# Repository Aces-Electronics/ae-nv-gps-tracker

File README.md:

# AE-SIM7080G-S3 NB-IoT Tracker

LilyGo T-SIM7080G-S3 based GPS tracker with NB-IoT connectivity for the AE-NV ecosystem.

## Hardware

- **Board**: LilyGo T-SIM7080G-S3 (ESP32-S3 + SIM7080G modem)
- **GPS**: Integrated GNSS (GPS/GLONASS/Beidou/Galileo)
- **Connectivity**: NB-IoT / LTE Cat-M1
- **Battery**: LiPo with AXP2101 PMU
- **Daughter board**: `ae-tracker-db` — LIS3DH accelerometer, SN65HVD231 CAN
  transceiver, and a BQ25176J charger that tops the LiPo up from the jetski's
  supply through an MCU-switchable cutoff. Plugs onto the LilyGo's 16-pin
  expansion header; the J4 pin map is in [`src/utilities.h`](src/utilities.h).

## Features

- ✅ GPS tracking with satellite count and HDOP
- ✅ NB-IoT connectivity via Telstra network
- ✅ MQTT telemetry publishing to AE-NV backend
- ✅ BLE configuration and diagnostics (15s window on cold boot, held open
  while a phone stays connected)
- ✅ Orientation detection (Flat/Vertical/Upside Down) — needs the daughter
  board; reports `Unknown` without it
- ✅ Configurable reporting intervals (1-60 minutes)
- ✅ Battery voltage monitoring
- ✅ Deep sleep between reports, with GPS-failure backoff
- ✅ **Daily heartbeat + wake on motion** — the timer is proof of life; movement
  is what actually triggers a report
- ✅ **Adaptive motion threshold** — climbs when the tracker keeps waking for
  movement GPS says didn't happen, drops straight back on real travel
- ✅ **Jetski engine data over CAN** — rpm, coolant, engine hours and iBR
  trim position decoded from the ECU (daughter board). See
  [`docs/can/seadoo-can.md`](docs/can/seadoo-can.md).

## Telemetry Fields

The tracker publishes the following data via MQTT:

```json
{
  "mac": "860016043157614",
  "model": "ae-sim7080g-tracker",
  "fix": true,               // Did this wake get a GPS fix at all
  "lat": -28.02575,          // lat/lon/alt/speed/sats/hdop are omitted if !fix
  "lon": 153.3879,
  "alt": -11.981,
  "speed": 0,
  "sats": 11,
  "supply_adc_raw": 9216,    // Ski supply, raw LIS3DH aux-ADC count
  "supply_voltage": 12.18,   // ...converted, once calibrated (absent if not)
  "voltage": 0.00,           // USB VBUS placeholder, debug frames only
  "device_voltage": 4.177,   // Internal battery voltage
  "battery_voltage": 4.177,  // Legacy alias
  "rssi": 19,
  "orientation": "Flat",
  "charge_state": "Charging",  // Charging | Idle | Fault | No Input
  "supply_enabled": true,      // Is the jetski allowed to feed the charger
  "wake_reason": "Motion",     // Cold Boot | Timer | Motion
  "accel_up": 1.00,            // Vehicle frame, g. Omitted if no IMU
  "accel_fwd": -0.02,
  "accel_stbd": 0.03,
  "engine_bus": true,          // Was the ski's CAN bus awake at all
  "ski_running": true,         // Drives the reporting cadence
  "rpm": 1455,                 // Omitted unless engine_bus
  "coolant_raw": 110,          // 0x102 b3, raw count — identity confirmed,
                               //   scaling not. raw-40 gives a believable 70C
  "engine_temp_raw": 140,      // 0x342 b4, raw count. NOT the coolant temp —
                               //   kept because it is a real signal, unidentified
  "engine_minutes": 5856,      // 0x342 b6:b7. Confirmed against the dash to the
                               //   minute: 5856 = 97h36m
  "ibr_trim": 5,               // 0x012 b2, iBR up/down position, 1..9
  "motion_sensitivity": "Medium", // Low | Medium | High -- the selected floor
  "motion_threshold_mg": 352,  // Where the adaptive ladder currently sits
  "motion_suppressed": 0,      // Motion wakes rate-limited away since last report
  "interval": 5,               // The RUNNING interval. A parked ski ignores it
  "next_wake_mins": 60         // When the next frame is actually due
}
```

## Development

### Prerequisites

- PlatformIO CLI or IDE
- USB-C cable for flashing

### Building & Flashing

```bash
# Build firmware
pio run -d /path/to/ae-sim7080g-tracker

# Flash to device
pio run -d /path/to/ae-sim7080g-tracker -t upload --upload-port /dev/ttyACM6

# Monitor serial output
pio device monitor --port /dev/ttyACM6 -b 115200
```

### CAN bring-up build

A separate environment boots straight into a listen-only CAN sniffer and never
reaches the tracker's normal cycle — no modem, no MQTT, no sleep:

```bash
pio run -e can-sniffer -t upload && pio device monitor -b 115200
```

It scans 250k → 500k → 125k, keeps whichever rate hears frames, prints a table
of distinct IDs with hit counts and per-byte ranges, then runs one probe: an
8-second learn phase, a single `*** GO ***`, and a 40-second window that records
every frame **and** narrates which bytes changed while you work a control.

The learn phase is the trick. It marks every byte that moves while the vehicle
is left alone — engine signals, counters, checksums — so afterwards it can
report only the bytes that held still and then moved. Operate one control and
the output is a short list naming that control's bytes.

Two things worth knowing before relying on it:

- **It prints its own blind spot.** A byte that moved during learning is hidden
  from the narration, which permanently hides both halves of any multiplexed
  signal. The excluded bytes are listed up front, and the CSV has every frame
  regardless — the narration is a convenience, the CSV is the evidence.
- **One prompt, then it halts.** Earlier versions recorded and narrated in
  separate phases with a `GO` for each, and the natural thing was to act on the
  second one, which was no longer recording. Three sessions were lost that way.

This is how the iBR up/down decode was found: the position byte and its command
byte both showed up in the narration within seconds of pressing a button.

**Listen-only never drives the bus**, not even the ACK bit, so this is safe to
plug into a running ski before anything is known about the bus or its rate. The
shipping firmware is unaffected — `default_envs` keeps this out of a bare
`pio run`, and the linker drops the sniffer and the TWAI driver from it.

Note that the daughter board's CAN termination jumper (JP1) is bridged by
default. A vehicle bus is already terminated at both ends, so JP1 most likely
wants cutting before connecting to a real ski.

### Configuration

The tracker can be configured via BLE during the 15-second window on cold boot,
or by holding the boot button through a reset. A connected client holds the
window open for as long as it stays, up to a five-minute ceiling — 15 seconds
is less than a connect, a service discovery and a look at the screen, so without
that the app was routinely cut off mid-session by the device closing BLE
underneath it. The ceiling is what stops a phone left connected in somebody's
pocket from holding the tracker out of deep sleep indefinitely.

- **Report Interval**: 1-60 minutes
- **Home Location**: Set via web UI
- **Admin Mode**: Forces 1-minute intervals for testing

#### BLE characteristics

Service `4fafc203-1fb5-459e-8fcc-c5c9c331914b`.

| Characteristic | UUID suffix | Direction | Payload |
| --- | --- | --- | --- |
| GPS | `…2030` | read/notify | `lat,lon,speed,sats,hdop,sats_in_view,fix` |
| Status | `…2031` | read/notify | `volts,soc,csq,Net: <creg>` |
| Name | `…2040` | read/write | device name suffix |
| Interval | `…2050` | read/write | uint32 LE, minutes |
| Motion sensitivity | `…2051` | read/write | one byte, 0 Low / 1 Medium / 2 High |
| Verbose telemetry | `…2052` | read/write | one byte, 0 off / non-zero on |
| Diagnostics: Device | `…2060` | read/notify | JSON |
| Diagnostics: Position | `…2061` | read/notify | JSON |
| Diagnostics: Power | `…2062` | read/notify | JSON |
| Diagnostics: Motion | `…2063` | read/notify | JSON |
| Diagnostics: Engine | `…2064` | read/notify | JSON |
| Pairing | `ACDC1234-…-1234567890CB` | read (encrypted) | trigger only |

Plus APN (`ae000101-…`) and the MQTT broker/user/pass characteristics
(`…2645`/`…2646`/`…2647`).

#### Pairing and what is gated

Bonding with MITM protection and Secure Connections, with a six-digit passkey
derived from the last three bytes of the Wi-Fi base MAC — the same derivation
every other AE product uses, and the same one the app displays.

This was previously off: the source said `// Security DISABLED for verification`,
which meant the PIN the app showed on the tracker screen was decoration. Nothing
ever asked for it, and anyone within radio range during a config window could
rewrite the APN, the broker and the MQTT credentials.

What is gated, and what is not:

- **Open** — the GPS and status characteristics. Someone close enough to read
  these over BLE is close enough to see the ski, so gating them buys little, and
  leaving them open means the app's basic screen works without a bond.
- **Encrypted (`READ_ENC`)** — all five diagnostics sections.
- **Encrypted (`WRITE_ENC`, and `READ_ENC` where readable)** — every
  configuration characteristic: name, APN, broker, MQTT user and password,
  interval, motion sensitivity, verbose telemetry.

The app reads the pairing characteristic on connect purely to force the link to
encrypt before it subscribes to anything — a subscribe on an encrypted
characteristic across an unencrypted link fails, and it fails quietly. That read
is service-agnostic in the app, so exposing the characteristic is all that was
needed on this side.

The device has no display, so the PIN comes from the app: it is shown against
the device while it is being connected to (which is when the OS prompts for it)
and on the tracker's own screen afterwards. It is also printed to the serial
console on every connect.

The GPS line's last two fields were appended to what was a five-field format,
so an older app reads the first five and ignores the rest. `sats_in_view` is the
number that moves during acquisition — `sats` counts the ones used in a fix and
sits at zero until there is one, so a screen showing only that looks broken for
two minutes and then works.

The five diagnostics characteristics carry the whole telemetry report, section
by section, refreshed once a second while a client is connected. They are built
by `buildTelemetry()` — the same function that builds the MQTT frame — so what
the app's debug screen shows is what the device publishes, by construction. They
are sectioned because a BLE characteristic value stops at 512 bytes and a full
verbose report is about twice that; `buildTelemetry()` decides which section each
field belongs to, so a field added later has to be given a home rather than
quietly failing to reach BLE.

Unlike the MQTT frame, the diagnostics are **always verbose**. The
`debug_payload` setting decides what is worth paying for over the cellular link;
it has nothing to say about what a phone already standing next to the ski may
look at.

## Debugging & Troubleshooting

### Serial Monitor

Monitor real-time debug output:

```bash
pio device monitor --port /dev/ttyACM0 -b 115200
```

### Debug Logging

The firmware includes comprehensive diagnostic logging:

**GPS Acquisition:**
```
[DEBUG] Raw CGNSINF: 1,1,20260206025753.000,-28.025740,153.387809,...
GPS FIX! Sats: 10 (lat: -28.02574, lon: 153.38780)
```

**Network Registration:**
```
[DEBUG] Checking network status...
[DEBUG] CEREG: +CEREG: 0,2  // 0,2 = registered on home network
[DEBUG] COPS: +COPS: 0,0,"Telstra Mobile",7  // Connected operator
[DEBUG] Signal Quality after registration: 20  // RSSI in dBm
```

**MQTT Publish:**
```
[DEBUG] Using Topic: ae-nv/tracker/860016043157614/up
[MQTT] Publishing Payload: {"mac":"860016043157614",...}
[MQTT] Publish OK
```

### Common Issues

**No GPS Fix:**
- Cold start can take 2-5 minutes
- Ensure clear view of sky
- Check antenna connection

**Network Registration Fails:**
- Verify SIM card is inserted and activated
- Check CEREG response: `0,0` = not registered, `0,2` = registered
- CSQ 99 = unknown signal (modem issue)
- CSQ 0-31 = valid signal strength

**MQTT Publish Fails:**
- Verify network registration succeeded first
- Check APN settings (default: `telstra.internet`)
- Ensure MQTT broker is reachable

**Device Not Appearing in UI:**
- Check MQTT payload in serial output
- Verify `mac` field matches device ID
- Check backend worker logs for ingestion errors
- Confirm device is claimed to your account

### Enable TinyGSM Debug

For detailed AT command logging, uncomment in `platformio.ini`:

```ini
build_flags = 
    -DTINY_GSM_DEBUG=Serial
```

This will show all modem AT commands and responses.

## Architecture

### GPS Parsing

The firmware uses robust satellite count parsing with fallback logic:
- Primary: "Satellites Used" from `+CGNSINF` response (index 15)
- Fallback: "Satellites in View" (index 14) when used count is unavailable

### Voltage Nomenclature

- `voltage`: External supply voltage (0.00V placeholder for future charging hardware)
- `device_voltage`: Internal PMU battery voltage (~4.2V when fully charged)
- `battery_voltage`: Legacy field for backward compatibility

### Power Management

- **Active Mode**: GPS acquisition + MQTT publish
- **BLE Window**: 15 seconds on cold boot, extended while a client is
  connected, to a five-minute ceiling
- **Charge cutoff**: the jetski feed is cut above **4.10V** and restored below
  **3.70V**, decided at report time against the PMU's battery reading and
  latched across sleep in RTC memory.

  4.10V sits *below* the BQ25176J's 4.2V regulation point, so the firmware —
  not the charger — is what ends a charge, opening the switch on the way up
  before the cell is ever held at full. The wide gap down to 3.70V is what makes
  that worth doing: a LiPo ages fastest sitting at full charge, so the pair
  cycles the cell through roughly 3.7–4.1 rather than floating it at 4.2. With
  only a sleeping tracker as a load, one traverse of that band takes a long time,
  so it costs very few cycles to buy. Both thresholds read the AXP2101's *cell*
  voltage — the jetski's own voltage is not available to decide on until the
  supply-sense divider is reworked.
- **Deep Sleep**: Cadence follows the ski, not the clock.
  - **Running** (CAN bus awake) → the configured `report_interval_mins`,
    5 minutes by default, settable over BLE. GPS-failure backoff applies
    (5/15/30/60/180 min).
  - **Parked** → a **1440-minute (daily) heartbeat**. GPS-failure backoff is not
    applied; stretching a day further on one missed fix trades away the only
    thing a heartbeat is for.

    **A parked heartbeat that fails to publish is retried sooner**, at 60 → 180
    → 360 minutes before falling back to the daily cadence. Without this, one
    bad modem session meant 48 hours of silence — and silence is
    indistinguishable from a stolen ski, a flat battery, or a dead tracker.
    Escalating rather than fixed because the usual cause is no coverage, and
    retrying hourly forever in a dead zone spends exactly the battery the daily
    cadence exists to protect.

    Note the daily timer is clocked by the ESP32's **internal RC oscillator**,
    not a crystal, so a 1440-minute sleep can legitimately land up to roughly an
    hour either side. A heartbeat that is late by tens of minutes is normal; one
    that is hours late is not.

  CAN traffic is the running signal because the ski's bus only wakes with the
  ignition. Supply voltage above ~13V would be the better test — it survives a
  CAN fault — but the supply-sense divider is mis-scaled and reads nothing
  usable yet (see `R15`/`R16` in [`src/utilities.h`](src/utilities.h)).
- **Wake on motion**: The LIS3DH interrupt is an `ext1` deep-sleep wake source.
  Motion reports are rate-limited to one per 120s, checked before the modem is
  powered, so a suppressed wake costs ~200ms rather than a GPS acquisition.

  **Tapping the board will not wake it, and that is the design.** `INT1_DURATION`
  is counted in ODR periods, so the default three samples at 50Hz require 60ms
  of *continuous* over-threshold motion, and normal mode band-limits to roughly
  ODR/2 = 25Hz before the comparator sees anything. A finger tap is a few
  milliseconds of mostly high-frequency energy — filtered down, and over long
  before the duration counter arrives. Shake the board instead.

  To check the path live rather than by waiting out a sleep cycle, the
  `db-bench` build watches INT1 for 15 seconds on startup and prints every
  latched event with the axes that caused it.

  On every wake from sleep the firmware reads the LIS3DH's interrupt block back
  *before* re-arming it and says whether it survived. Those registers are
  volatile, so retained values prove the part held its 3.3V rail through the
  sleep and reset defaults prove it did not — which settles the question a
  missed wake otherwise only raises. (It should always survive: the daughter
  board's 3V3 is J4.1 = AXP2101 DCDC1, the same rail that keeps the ESP32's own
  RTC domain alive. Nothing in this firmware touches DCDC1.)
- **Motion sensitivity**: three selectable levels, each setting the **floor** of
  the adaptive ladder rather than a fixed threshold — the ski still finds its own
  level from wherever it starts. Values are chosen against a *measured* noise
  floor of 24mg (high-pass filter settled, board at rest), so the margins are
  known rather than guessed:

  | Level | Floor | Margin | Ceiling | For |
  |---|---|---|---|---|
  | Low | 704mg | ~29× noise | 2032mg | A deliberate shove; a ski somewhere lively, where less would report the weather |
  | **Medium** | **352mg** | ~15× noise | **1408mg** | **Shipped default.** Registers ordinary handling |
  | High | 256mg | ~11× noise | 1024mg | A quiet mooring, where a nudge should count |

  These were **doubled** from an original 352/176/128 after the first real
  deployment: a unit on Medium riding in a car woke nine times in 65 minutes and
  spent the hour climbing away from a floor too low to start from. The old
  Medium is the new Low, which is the honest description of what 176mg proved
  to be worth.

  All three sit exactly on the `INT1_THS` grid (16mg steps at ±2g) — 44, 22 and
  16 counts — so none truncate. Worth checking when retuning: 56mg, for example,
  is not representable and would silently become 48mg, only 2× the noise floor.

  Settable over BLE on characteristic `beb5483e-36e1-4688-b7f5-ea07361b2051`
  (read/write, one byte: `0` Low, `1` Medium, `2` High). A write out of that
  range is rejected rather than clamped — clamping would silently land on
  Medium and the value read back afterwards would not be the one sent. The
  change takes effect **immediately**, re-arming the accelerometer rather than
  waiting for the next boot, which for a parked ski would be a day away.

  `motion_sensitivity` and `motion_threshold_mg` are published on **every**
  frame, not just debug ones. They used to be gated behind `debug` directly
  under a comment saying they existed so the adaptive logic could be seen from
  the backend rather than a serial cable — which the gate prevented. A unit sat
  at 528mg on a 176mg floor for an hour and nothing in the cloud said so.

  **TODO — web UI control.** The setting is stored in NVS (`mot_sens`), carried
  in `TrackerSettings.motion_sensitivity`, published as `motion_sensitivity`,
  and writable over BLE — but the web app has no control for it yet.

- **Adaptive threshold**, which moves in *both* directions:

  **Up.** After a motion wake, GPS arbitrates: a fix is *travel* if it shows
  2 km/h or more, **or** if it has moved 100m or more from the reference
  position. Anything else counts as unexplained, and three consecutive
  unexplained wakes raise the threshold one step. A wake with *no* fix changes
  nothing — a garage roof is not a false positive.

  Step and ceiling both **scale with the selected floor** (step = the floor,
  ceiling = 4× it), so three unexplained wakes cost the same fraction of the
  range at every setting. They used to be flat 176mg/1408mg — Medium's numbers
  applied to everything — which made the control a floor and nothing else: a
  unit on High could be walked to eleven times the sensitivity its owner asked
  for. `INT1_THS` caps the ceiling at 2032mg (7 bits, 16mg steps at ±2g), which
  is why Low's 2816mg is clamped.

  **Position is gated on PDOP**, not HDOP. Measured on a stationary bench, two
  fixes three seconds apart read 35m apart: one at PDOP 25.0, the other at PDOP
  2.0. HDOP on the bad one was a respectable 3.9 — the error was almost entirely
  vertical (VDOP 24.7), so only PDOP shows it. A DOP of `0` means the field was
  absent, not that the fix was perfect, and is refused everywhere.

  **Up, faster, on rate alone.** Motion wakes inside the 120s report limit are
  counted rather than discarded. Ten of them between two reports raises the
  threshold immediately, without waiting for GPS — the rate *is* the evidence,
  and those wakes are precisely the ones that never got a fix to be judged by.
  Previously they were invisible to this logic, which left a hole exactly where
  it was most needed: a hull working against a mooring produces mostly
  suppressed wakes.

  **Down.** Genuine travel resets straight to the floor — that is proof the
  tracker should be at its most sensitive, and it contradicts whatever evidence
  built the climb. Failing that, three consecutive reports with *no* motion
  activity at all (no wake, none suppressed) ease it down one step. Without
  this the ladder is a ratchet, and a ski moved to a calmer berth stays deaf
  forever — the worst failure available here, because it is self-sustaining:
  the deafer it gets, the less likely anything crosses the threshold to say
  otherwise, including a theft.

  The current value is persisted in NVS and published as `motion_threshold_mg`,
  next to `motion_sensitivity` so a false-wake report can tell what was chosen
  from what the ski decided, and `motion_suppressed` so the wake rate is visible
  at all.

  Changing the floor — by firmware retune or by the setting — discards a stored
  threshold derived from a different one, so a change actually reaches a unit
  that already has a value saved.

- **Wake LED**: the AXP2101 charge LED is lit while awake and switched off
  immediately before every deep sleep, so a dark unit is a sleeping one. A
  **4Hz blink instead of steady means the wake came from the accelerometer**,
  which is the only way to tell a motion wake from a timer wake on battery,
  where there is no serial port. Note this takes the LED away from the charger's
  own control; charge state is reported over MQTT instead.

  (`NEOPIXEL_PIN` in [`utilities.h`](src/utilities.h) is inherited from other S3
  boards and drives nothing — this board has no addressable RGB LED. The
  remaining `strip` calls in `main.cpp` are dead code.)

No migration is needed for already-provisioned trackers: a stored 5-minute
interval now describes the *running* case, which is what it was always for.

### Ski supply voltage

The daughter board divides the jetski supply into the LIS3DH's auxiliary ADC.
With **R16 swapped to 200k** the divider is 1.8M/200k = **1/10**, mapping 8–16V
onto 800–1600mV — which is the LIS3DH aux ADC's actual window (1200mV ±400mV).

**The divider taps `SUPPLY`, downstream of the TPS1H000 switch**, so it reads
nothing whenever the charge policy has the feed cut — which is most of the time
by design. `powerReadSupplyRaw()` therefore closes the switch briefly (200ms
settle, covering six time constants of 180k × 100nF as well as the switch's own
turn-on), takes the sample, and restores the switch to exactly the state it was
in. Leaving it closed because a measurement happened would quietly undo the
charge cutoff.

**Calibration is two-point and measured, not derived.** ST does not document
whether the aux-ADC code is inverted, and the real ratio depends on resistor
tolerance and an input impedance ST does not specify — so a formula from the
schematic would be a guess wearing a unit. Measured on hardware:

| point | meter | raw | 10-bit |
|---|---|---|---|
| low | 12.06V | 10188 | 159 |
| high | 14.33V | −7508 | −118 |

**The code is inverted** — 0V reads 32512, and the count falls as voltage rises.
That is exactly the ambiguity the datasheet leaves open, and it is why this is
measured. The slope works out at ~122 counts/V against ~128 predicted from the
design, i.e. within ~5% — comfortably inside resistor tolerance.

To calibrate a board, flash the `supply-cal` environment and drive it over
serial: `L <volts>` and `H <volts>` store the two points into the same NVS keys
the tracker reads (`sup_raw_lo`/`sup_v_lo`, `sup_raw_hi`/`sup_v_hi`). Readings
are averaged over 16 samples, because one sample of a 10-bit ADC on a 180k
source is noisy enough to bake that noise into the fit. `supply_voltage` is
published only once both points exist; until then only `supply_adc_raw` goes
out, so an uncalibrated unit reports nothing rather than something wrong.

**Useful range is ~8–16V.** Below about 8V the ADC floors and the reading is
optimistic — a flat jetski battery reads around 9V rather than as flat.

Note `charge_state: "Fault"` with **no LiPo attached** is expected: the
BQ25176J blinks STAT when it has nothing to charge.

### OTA downloads

Downloads used to die part-way with `+CAURC: buffer full` followed by
`Socket closed early` — 397468 of 680816 bytes on the observed failure.

The cause is arithmetic, not a bug. TinyGSM drains a socket **one byte at a
time** over the modem UART, and at 115200 baud that is ~11.5 KB/s. LTE Cat-M1
delivers up to ~37 KB/s, so the network fills the modem's socket buffer about
three times faster than it can be emptied — which is precisely what
`+CAURC: buffer full` reports. A 680 KB image also needs ≥59s of pure UART time
at 115200 before any AT overhead.

Three changes:

- **The modem UART is raised to 921600 for the transfer** (~92 KB/s), so the
  UART stops being the constraint rather than merely keeping pace. Restored to
  115200 afterwards: `AT+IPR` is not persisted without `AT&W`, so a modem left
  fast would be unreachable on the next boot when `Serial1` opens at 115200.
  The switch verifies the link at the new rate and reverts on failure — the only
  remote repair path for a fielded tracker is the OTA itself, so a half-applied
  baud change would be unrecoverable. Both 460800 and 921600 were confirmed on
  hardware with the `baud-test` environment.
- **`TINY_GSM_DEBUG` is no longer in the release build.** It prints a line per
  data URC — ~660 of them per OTA — onto the same serial port the download is
  competing with. Use the `modem-debug` environment when AT tracing is wanted.
- **The empty-poll delay is 2ms rather than 20ms**, and throughput is logged in
  KB/s, so a future failure can be read rather than guessed at.

## Known Issues

1. **BLE Connection**: Some devices experience connection stability issues (see agent prompt)
2. **Power Consumption**: No deep sleep implementation yet (see agent prompt)
3. **GPS Cold Start**: Can take 2-5 minutes for initial fix

## Web UI Integration

The tracker integrates with the AE-NV web dashboard:

- **Live Map**: Real-time GPS position with historical track
- **Battery Card**: Displays internal battery voltage
- **Supply Card**: Displays external supply (0V placeholder)
- **Satellite Count**: Live satellite visibility
- **Recent Locations**: Historical table with GPS, battery, and supply data

## Forensic Crash Reporting
The tracker includes a high-fidelity crash handling system for remote diagnostics:
- **Panic Interception**: Intercepts ESP32-S3 hardware panics to capture the exact state of failure.
- **Persistent Logs**: Saves register dumps and backtraces to NVS/RTC memory to survive reboots.
- **Cloud Delivery**: Automatically uploads the crash log to the cloud via MQTT on next boot.
- **Symbol Matching**: The CI pipeline preserves `.elf` files for every build, allowing the backend to translate raw addresses into source code lines (e.g., `main.cpp:142`).

## Next Steps

See the agent prompts in `/docs/agent-prompts/` for:
1. BLE connection debugging
2. Low-power mode implementation with power profiler analysis

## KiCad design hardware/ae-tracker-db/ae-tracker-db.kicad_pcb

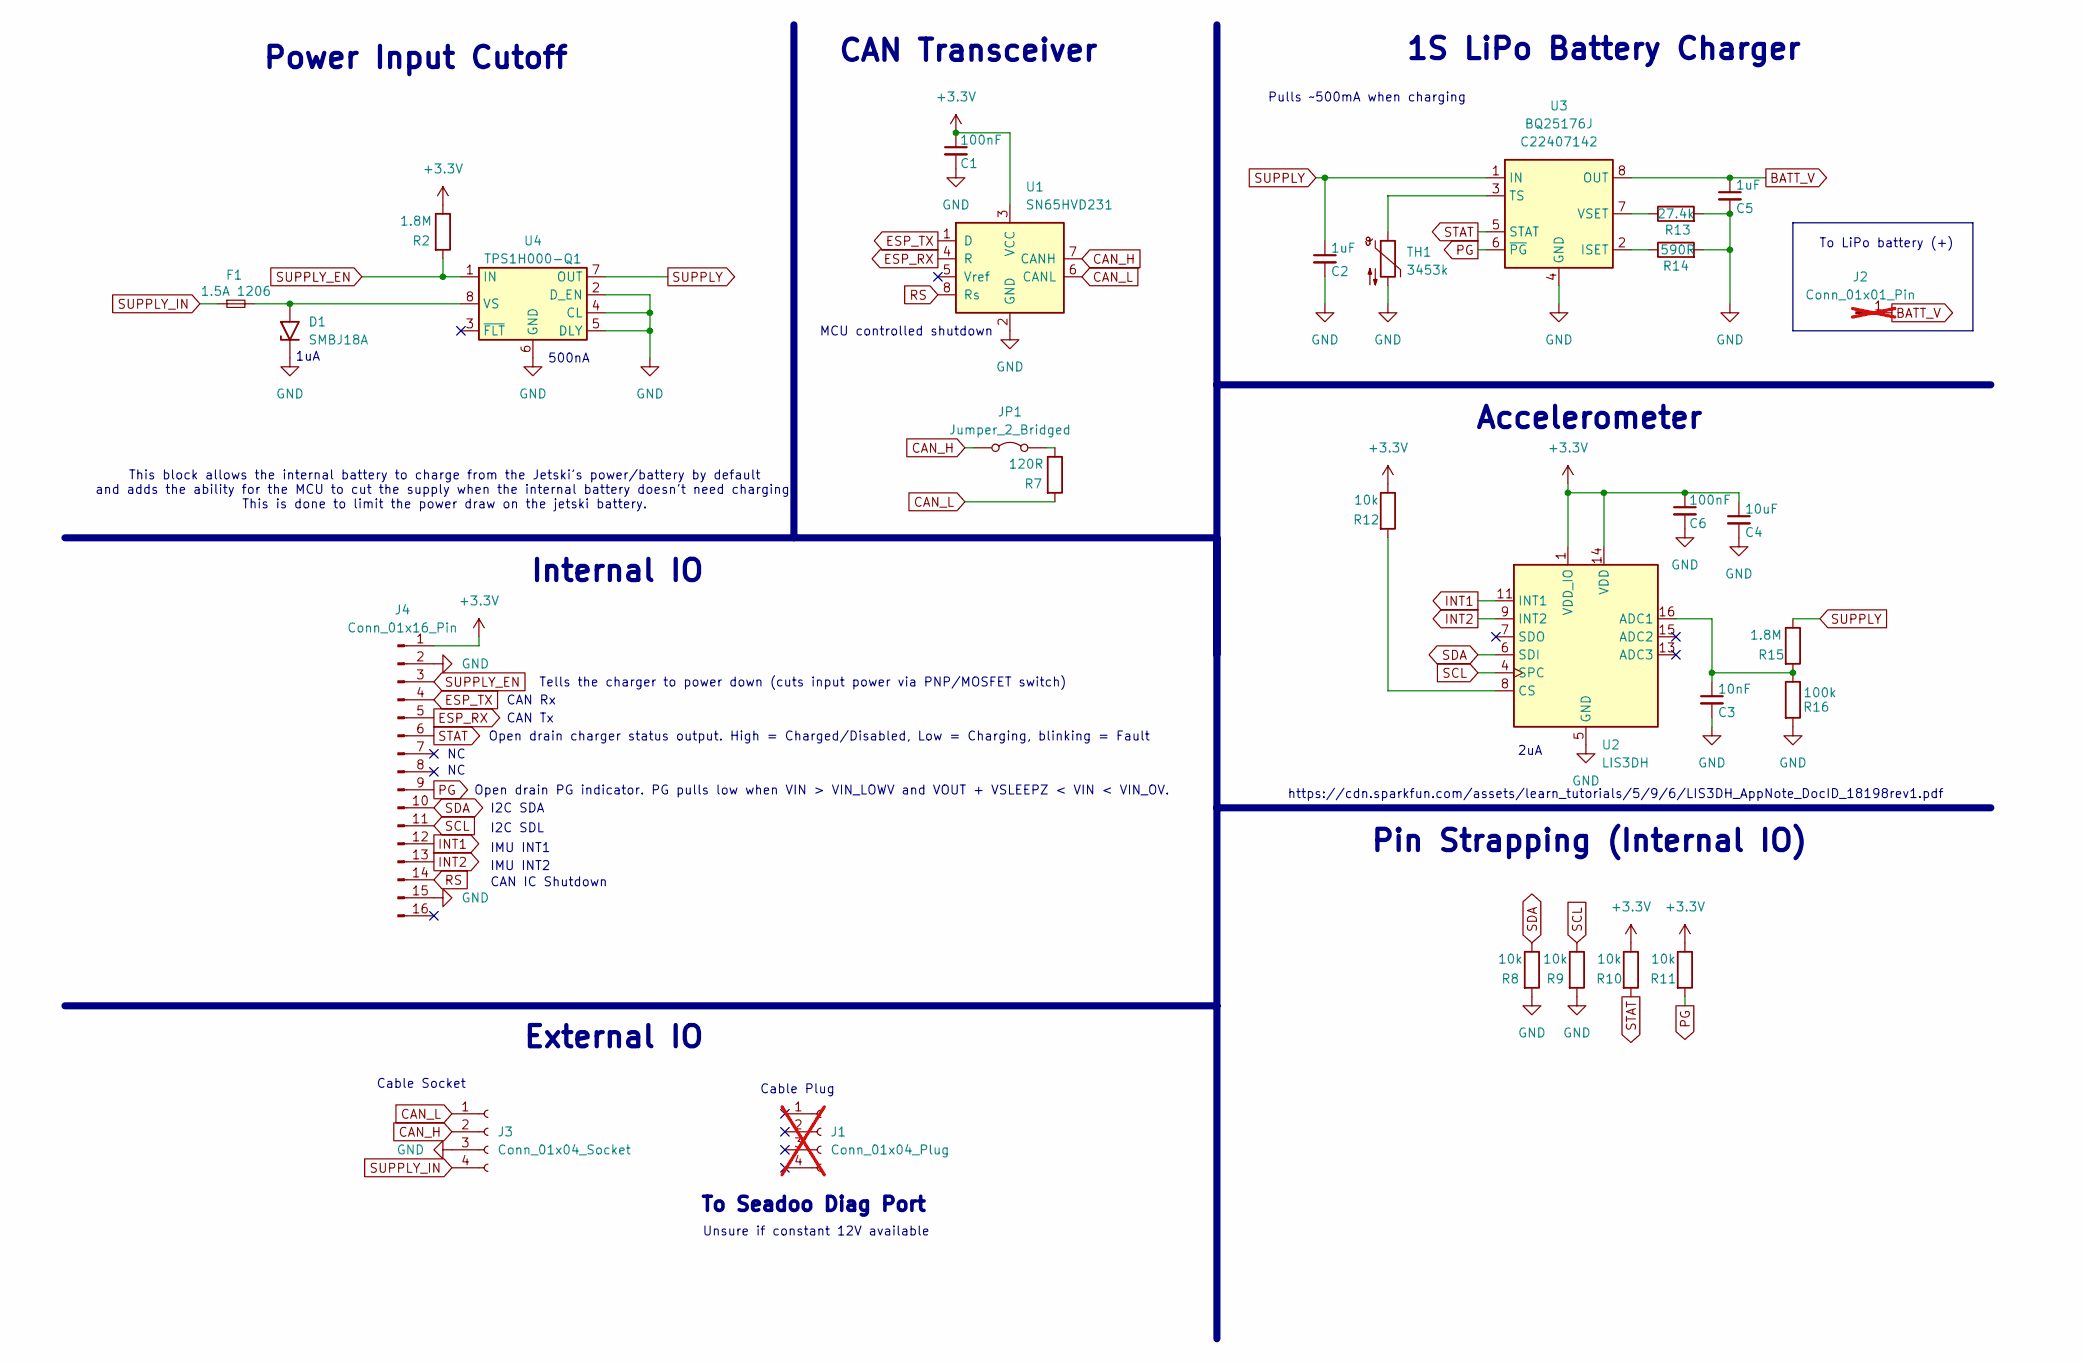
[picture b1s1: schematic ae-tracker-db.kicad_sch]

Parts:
C1, C6: 100nF; C_0603_1608Metric; LCSC C14663
C2, C5: 1uF; C_0603_1608Metric; LCSC C15849
C3: 10nF; C_0603_1608Metric; LCSC C57112
C4: 10uF; C_0603_1608Metric; LCSC C19702
D1: SMBJ18A; D_SMB; LCSC C78412
F1: 1.5A 1206; R_1206_3216Metric; LCSC C41367222
J1: Conn_01x04_Plug; PinHeader_1x04_P2.54mm_Vertical; LCSC C2923037; not fitted
J2: Conn_01x01_Pin; PinHeader_1x01_P2.54mm_Vertical; not fitted
J3: Conn_01x04_Socket; PhoenixContact_MC_1,5_4-GF-3.5_1x04_P3.50mm_Horizontal_Thre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; LCSC C441259
J4: Conn_01x16_Pin; PinHeader_1x16_P2.54mm_Horizontal; LCSC C2894958
JP1: Jumper_2_Bridged; SolderJumper-2_P1.3mm_Bridged_RoundedPad1.0x1.5mm
R2, R15: 1.8M; R_0603_1608Metric; LCSC C13318
R7: 120R; R_0603_1608Metric; LCSC C22787
R8, R9, R10, R11, R12: 10k; R_0603_1608Metric; LCSC C25804
R13: 27.4k; R_0603_1608Metric; LCSC C22964
R14: 590R; R_0603_1608Metric; LCSC C2933241
R16: 100k; R_0603_1608Metric; LCSC C25803
TH1: 3453k; R_0603_1608Metric; LCSC C406719
U1: SN65HVD231; SOIC-8_3.9x4.9mm_P1.27mm; LCSC C129257
U2: LIS3DH; LGA-16_3x3mm_P0.5mm_LayoutBorder3x5y; LCSC C15134
U3: BQ25176J; WSON-8-1EP_2x2mm_P0.5mm_EP0.9x1.6mm; LCSC C22407142
U4: TPS1H000-Q1; MSOP-8-1EP_3x3mm_P0.65mm_EP1.68x1.88mm; LCSC C2653764

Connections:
+3.3V: C1.1, C4.1, C6.1, J4.1, R2.1, R10.1, R11.1, R12.1, U1.3 (VCC), U2.1 (VDD_IO), U2.14 (VDD)
BATT_V: C5.1, J2.1, U3.8 (OUT)
CAN_H: J3.2, JP1.1 (A), U1.7 (CANH)
CAN_L: J3.1, R7.2, U1.6 (CANL)
ESP_RX: J4.5, U1.4 (R)
ESP_TX: J4.4, U1.1 (D)
GND: C1.2, C2.2, C3.2, C4.2, C5.2, C6.2, D1.1 (A1), J3.3, J4.2, J4.15, R8.2, R9.2, R13.2, R14.2, R16.2, TH1.2, U1.2 (GND), U2.5 (GND), U2.10 (GND), U2.12 (GND), U3.4 (GND), U3.9 (GND), U4.2 (D_EN), U4.4 (CL), U4.5 (DLY), U4.6 (GND), U4.9 (GND)
INT1: J4.12, U2.11 (INT1)
INT2: J4.13, U2.9 (INT2)
unnamed: D1.2 (A2), F1.2, U4.8 (VS)
unnamed: JP1.2 (B), R7.1
unnamed: C3.1, R15.2, R16.1, U2.16 (ADC1)
unnamed: R12.2, U2.8 (CS)
unnamed: R14.1, U3.2 (ISET)
unnamed: TH1.1, U3.3 (TS)
unnamed: R13.1, U3.7 (VSET)
PG: J4.9, R11.2, U3.6 (~PG)
RS: J4.14, U1.8 (Rs)
SCL: J4.11, R9.1, U2.4 (SPC)
SDA: J4.10, R8.1, U2.6 (SDI)
STAT: J4.6, R10.2, U3.5 (STAT)
SUPPLY: C2.1, R15.1, U3.1 (IN), U4.7 (OUT)
SUPPLY_EN: J4.3, R2.2, U4.1 (IN)
SUPPLY_IN: F1.1, J3.4

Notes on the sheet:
CAN Transceiver
IMU INT2
Cable Socket
Internal IO
1uA
Open drain charger status output. High = Charged/Disabled, Low = Charging, blinking = Fault
Open drain PG indicator. PG pulls low when VIN > VIN_LOWV and VOUT + VSLEEPZ < VIN < VIN_OV.
Accelerometer
Tells the charger to power down (cuts input power via PNP/MOSFET switch)
CAN Tx
External IO
This block allows the internal battery to charge from the Jetski's power/battery by default and adds the ability for the MCU to cut the supply when the internal battery doesn't need charging. This is done to limit the power draw on the jetski battery.
I2C SDL
MCU controlled shutdown
Unsure if constant 12V available
CAN Rx
1S LiPo Battery Charger
Pulls ~500mA when charging
To Seadoo Diag Port
CAN IC Shutdown
Cable Plug
https://cdn.sparkfun.com/assets/learn_tutorials/5/9/6/LIS3DH_AppNote_DocID_18198rev1.pdf
2uA
IMU INT1
Pin Strapping (Internal IO)
I2C SDA
500nA
Power Input Cutoff
To LiPo battery (+)

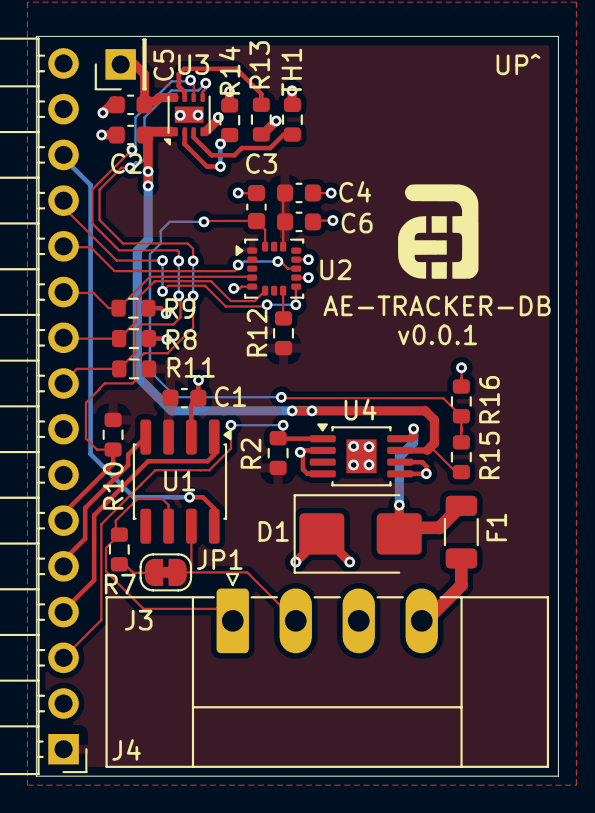
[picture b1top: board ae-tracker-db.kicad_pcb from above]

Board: 2 copper layers, 29.0 x 41.1 mm, 28 parts (0 on the bottom side), 24 nets.

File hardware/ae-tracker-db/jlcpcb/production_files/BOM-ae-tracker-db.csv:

Comment,Designator,Footprint,LCSC,Quantity
1.5A 1206,F1,R_1206_3216Metric,C41367222,1
1.8M,"R15,R2",R_0603_1608Metric,C13318,2
100k,R16,R_0603_1608Metric,C25803,1
100nF,"C1,C6",C_0603_1608Metric,C14663,2
10k,"R10,R11,R12,R8,R9",R_0603_1608Metric,C25804,5
10nF,C3,C_0603_1608Metric,C57112,1
10uF,C4,C_0603_1608Metric,C19702,1
120R,R7,R_0603_1608Metric,C22787,1
1uF,"C2,C5",C_0603_1608Metric,C15849,2
27.4k,R13,R_0603_1608Metric,C22964,1
3453k,TH1,R_0603_1608Metric,C406719,1
590R,R14,R_0603_1608Metric,C2933241,1
BQ25176J,U3,WSON-8-1EP_2x2mm_P0.5mm_EP0.9x1.6mm,C22407142,1
Conn_01x04_Socket,J3,"PhoenixContact_MC_1,5_4-GF-3.5_1x04_P3.50mm_Horizontal_ThreadedFlange",C441259,1
Conn_01x16_Pin,J4,PinHeader_1x16_P2.54mm_Horizontal,C2894958,1
LIS3DH,U2,LGA-16_3x3mm_P0.5mm_LayoutBorder3x5y,C15134,1
SMBJ18A,D1,D_SMB,C78412,1
SN65HVD231,U1,SOIC-8_3.9x4.9mm_P1.27mm,C129257,1
TPS1H000-Q1,U4,MSOP-8-1EP_3x3mm_P0.65mm_EP1.68x1.88mm,C2653764,1
Conn_01x01_Pin,,PinHeader_1x01_P2.54mm_Vertical,,0
Jumper_2_Bridged,JP1,SolderJumper-2_P1.3mm_Bridged_RoundedPad1.0x1.5mm,,1

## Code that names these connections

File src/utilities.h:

#pragma once

// The LILYGO_T_SIM7080G_S3 board marker is set in platformio.ini's build_flags,
// which is where it reaches libraries as well as this header. It was defined
// here too until every file including this one warned about redefining it.
// Nothing in the tree tests it -- the LilyGo original picked a pin block with
// it and those conditionals are long gone -- so the second copy bought nothing.

// Modem Pins (T-SIM7080G-S3)
#define MODEM_TX             5
#define MODEM_RX             4
#define MODEM_PWRKEY         41
#define MODEM_DTR            42
#define MODEM_RI             3

// I2C Pins (SDA=15, SCL=7)
#define I2C_SDA              15
#define I2C_SCL              7

// PMU / Battery Pins
#define PMU_IRQ              6
#define ONE_WIRE_PIN         42 
#define BAT_ADC_PIN          1  // Battery Voltage ADC

// Telemetry/Status LEDs (NeoPixel)
#define NEOPIXEL_PIN         48 // Built-in RGB on some S3 boards, check specific revision
#define NEOPIXEL_COUNT       1

// GPS/GNSS is internal to the SIM7080G, accessed via AT commands

// ---------------------------------------------------------------------------
// AE Tracker Daughter Board (hardware/ae-tracker-db) -- 16-pin header J4
//
// J4 plugs onto the LilyGo's expansion header. The mapping below is locked at
// both ends: J4.1/J4.2 are 3V3/GND and J4.15/J4.16 are GND/DC5, which is
// exactly how the LilyGo pinout brackets those twelve GPIOs.
//
// J4.7 (GPIO3) and J4.8 (GPIO46) are deliberately NC. Both are ESP32-S3
// strapping pins, and GPIO3 is already MODEM_RI on this board.
//
// Every pin below is GPIO0-21, so all of them are RTC GPIOs: they can hold a
// level across deep sleep, and the IMU interrupts can act as ext1 wake sources.
// ---------------------------------------------------------------------------

// CAN -- SN65HVD231 (U1). The S3's TWAI controller routes to any GPIO.
#define DB_CAN_TX            17 // J4.4  -> U1.1 (D), transceiver driver input
#define DB_CAN_RX            18 // J4.5  -> U1.4 (R), transceiver receiver output

// SN65HVD231 Rs: LOW = high-speed mode, HIGH = standby (~370uA). Nothing on the
// board biases it, so it floats until firmware drives it -- drive LOW before
// opening the bus, HIGH before deep sleep.
#define DB_CAN_RS            14 // J4.14 -> U1.8 (Rs)

// IMU -- LIS3DH (U2). This is a SECOND I2C bus; the AXP2101 PMU keeps the
// I2C_SDA/I2C_SCL pair above, and these pins are not shared with it.
#define DB_IMU_SDA           10 // J4.10 -> U2.6 (SDI)
#define DB_IMU_SCL           11 // J4.11 -> U2.4 (SPC)
#define DB_IMU_INT1          12 // J4.12 -> U2.11 (INT1)
#define DB_IMU_INT2          13 // J4.13 -> U2.9 (INT2)

// U2 CS is strapped high through R12, selecting I2C.
//
// SDO/SA0 is left floating on the board. The LIS3DH carries an internal
// pull-up on that pin (~20.4k typ, datasheet Table 3), NOT a pull-down, so
// floating sits high and the expected address is 0x19. Both are probed anyway,
// and imuBegin() logs which one answered.
//
// Worth knowing before anyone "fixes" the float by strapping SA0 to GND: that
// would select 0x18, but it also puts the rail across the internal pull-up for
// ~162uA continuously at 3.3V -- on its own more than the <100uA deep-sleep
// budget. Tie it to VDD_IO if determinism is wanted; that keeps 0x19 and costs
// nothing. Grounding it is only sensible alongside CTRL_REG0 (0x1E) = 0x90,
// which disables the pull-up.
#define DB_IMU_ADDR_LOW      0x18
#define DB_IMU_ADDR_HIGH     0x19

// Standard-mode I2C. The socketed board carries real pull-ups on both lines --
// confirmed by making each win against the S3's internal pull-down, SDA at
// 3101mV and SCL at 3093mV -- so the bus no longer depends on the ~45k
// internals that forced this down to 50kHz on the earlier boards.
//
// imuBegin() measures the pull-ups on every boot and says which it found, so a
// board without them shows up in the log rather than as mysterious timeouts.
#define DB_I2C_HZ            100000

// Charger -- BQ25176J (U3), behind the TPS1H000-Q1 (U4) supply switch.
//
// SUPPLY_EN carries a 1.8M pull-up to 3.3V (R2), so the jetski supply is ON by
// default: while the ESP32 is in reset, unflashed, or asleep with the pin
// released. Driving it LOW is the only thing that stops the board drawing from
// the jetski battery.
#define DB_SUPPLY_EN         16 // J4.3  -> U4.1 (IN)

// Both open-drain with 10k pull-ups (R10/R11), so both idle HIGH.
// STAT: LOW = charging, HIGH = charged or disabled, blinking = fault.
// PG is active low: LOW = input supply present and within the charger's window.
#define DB_CHG_STAT          8  // J4.6  -> U3.5 (STAT)
#define DB_CHG_PG            9  // J4.9  -> U3.6 (~PG)

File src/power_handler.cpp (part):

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    // other readings rather than being averaged into them.
    if (!ps.supplyPresent) {
        // Checked before the blink test on purpose. With no input the charger
        // is not driving STAT at all, so a pin wandering between reads is noise
        // on an open-drain line with nothing on it -- reporting that as a
        // charger fault is how a parked, healthy ski ends up looking broken.
        ps.state = ChargeState::NoInput;
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        ps.state = ChargeState::Idle;
    }

    Serial.printf("[Power] SUPPLY_EN pin reads %s\n",
                  digitalRead(DB_SUPPLY_EN) == HIGH ? "HIGH (switch on)" : "LOW (switch off)");
    Serial.printf("[Power] PG=%s STAT=%s -> %s (supply %s)\n",
                  ps.supplyPresent ? "present" : "absent",
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    gpio_hold_en((gpio_num_t)DB_CAN_RS);
    gpio_deep_sleep_hold_en();

    Serial.printf("[Power] Sleeping with jetski supply %s\n",
                  s_supplyEnabled ? "enabled" : "cut");
}

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                  (ctlSda && ctlScl) ? "" : "   <-- CONTROL FAILED, distrust the rest");

    int statMv = 0, pgMv = 0;
    const bool stat = hasExternalPullup(DB_CHG_STAT, statMv);
    const bool pg   = hasExternalPullup(DB_CHG_PG, pgMv);
    Serial.printf("[Power] R10 on STAT: %s (%d mV)   R11 on PG: %s (%d mV)\n",
                  stat ? "FITTED" : "none", statMv, pg ? "FITTED" : "none", pgMv);
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
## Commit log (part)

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2026-02-06 Initial commit: One-Shot logic with BLE config
2026-02-06 Fix GPS sats parsing and shorten test interval to 2 mins
2026-02-06 Refine Stay Awake logic and force automatic operator selection (COPS=0)
2026-02-06 fix: correct voltage nomenclature for tracker (voltage=supply, device_voltage=battery)
2026-02-06 docs: add debugging and troubleshooting section to README
2026-02-06 ble wip
2026-02-06 fixing bugs
2026-02-06 fixes
2026-02-16 power saving fixes
2026-02-16 Fixing sats decode
2026-02-16 more fixes
2026-02-21 v0.0.1 off to JLCPCB
2026-02-25 v0.0.2 WIP
2026-02-26 feat(ci): add GitHub Actions build-and-release workflow
2026-02-27 fix(ci): use Python heredoc for HMAC signing in Notify step
2026-02-27 fix(ci): use inline Python for HMAC to avoid YAML heredoc syntax errors
2026-02-27 fix(ci): set compression-level 0 for artifacts so server can extract zip
2026-02-28 feat: implement unified crash handling and elf artifact generation
2026-02-28 fix: resolve CI build failure by adding shared crash handler library
2026-02-28 fix: relocate lib_extra_dirs to env section for PlatformIO compatibility
2026-02-28 fix: restore dependency isolation and use file:// for shared library
2026-02-28 fix: embed crash handler library for self-contained CI builds
2026-03-11 ci: add action to cleanup old artifacts to save quota
2026-03-11 ci: replace aggressive gc with native 1-day retention due to deadlock
2026-03-11 Fixing wrong part number
2026-03-19 Adding box label
2026-03-27 ci: optimize github actions cache storage
2026-03-27 ci: remove pip cache to fix setup-python error
2026-05-08 chore: ignore DS_Store and remove .history
2026-05-10 chore: add hw_version payload to webhook
2026-05-22 git: ignore .vscode folder and add database backups pattern
